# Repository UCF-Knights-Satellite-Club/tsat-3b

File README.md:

# tsat-3b

TSat-3B: a 1.5U CubeSat that is dropped from a tethered balloon and flies itself back to the launch site under a guided parafoil.
This repo holds the flight software and every circuit board.

## What's here

| Folder | What it is | Status |
|---|---|---|
| [`FlightController/`](FlightController/) | ESP32 guided-parafoil flight software (Arduino sketch) plus a PC simulator | Guidance done and tested in simulation; sensor drivers still stubbed |
| [`PowerDistributionBoard/1.5U-Rev1/`](PowerDistributionBoard/1.5U-Rev1/) | Power board candidate (Eric P.): carrier for plug-in buck modules | Under review |
| [`PowerDistributionBoard/TPSM63610/`](PowerDistributionBoard/TPSM63610/) | Power board candidate (Lawson H.): on-board TPSM63610 regulators | Under review |
| [`PowerDistributionBoard/RevB-SY8105/`](PowerDistributionBoard/RevB-SY8105/) | Earlier power board (Lawson H.), on-board SY8105 regulators | Superseded |
| [`MainBoard/`](MainBoard/) | Flight computer board (Pablo J.): ESP32, IMU, GPS, barometer, LoRa | Not uploaded yet |

Two power board designs are being reviewed to pick the one going forward. See [`PowerDistributionBoard/README.md`](PowerDistributionBoard/README.md) for how they compare.

## Contributing

Read [`CONTRIBUTING.md`](CONTRIBUTING.md) before you upload anything. In short: upload the KiCad project together with its
Gerbers, put files in the right folder, don't upload zips of whole projects, and write one sentence in the PR description.

## License

- Software (`FlightController/`): [MIT](LICENSE)
- Hardware designs (`PowerDistributionBoard/`, `MainBoard/`): [CERN Open Hardware Licence v2, Permissive (CERN-OHL-P-2.0)](LICENSE-HARDWARE)

Copyright (c) 2026 Knights Satellite Club

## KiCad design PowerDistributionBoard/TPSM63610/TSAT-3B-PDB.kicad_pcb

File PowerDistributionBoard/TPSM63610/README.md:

# TSAT-3B-PDB (on-board TPSM63610 regulators)

<p align="center">
  <b>Candidate, under review</b> &nbsp;·&nbsp; Designer: Lawson H. &nbsp;·&nbsp; 70 × 67 mm &nbsp;·&nbsp; 2-layer &nbsp;·&nbsp; KiCad 10
</p>

| Top | Bottom |
|:---:|:---:|
|  |  |

📄 **Schematic:** [PDF](docs/schematic.pdf) &nbsp;·&nbsp; 🧾 **BOM:** [CSV with suppliers](bom/TSAT-3B-PDB_BOM.csv)
&nbsp;·&nbsp; 🔌 **Wiring:** [notes](docs/wiring.md) &nbsp;·&nbsp; 📝 [Review log](docs/review-notes.md)

70 parts. Two TI TPSM63610 buck modules on the board make 5.0 V logic and 7.2 V servo power from a 3S battery. It also has a main
input switch, fused outputs for two servos, a nichrome cutter channel, external brake resistors, battery voltage sensing and a 5 V
output for a camera board. Some 3D models are missing, so the renders show bare pads for the TPSM63610s and a few connectors.

- Open `TSAT-3B-PDB.kicad_pro` in KiCad 10. The symbol and footprint libraries it needs are in `Libraries/`.
- No Gerbers yet. Export them once this design is chosen.

Unpacked from `TSAT-3B-PDB.zip` (uploaded in PR #2). The lock files, KiCad local settings, the `.history/` folder and the review
tool output (`Review/`, `.patch`) from that zip were left out.

## Review

Design review feedback is tracked in [issue #8](https://github.com/UCF-Knights-Satellite-Club/tsat-3b/issues/8).

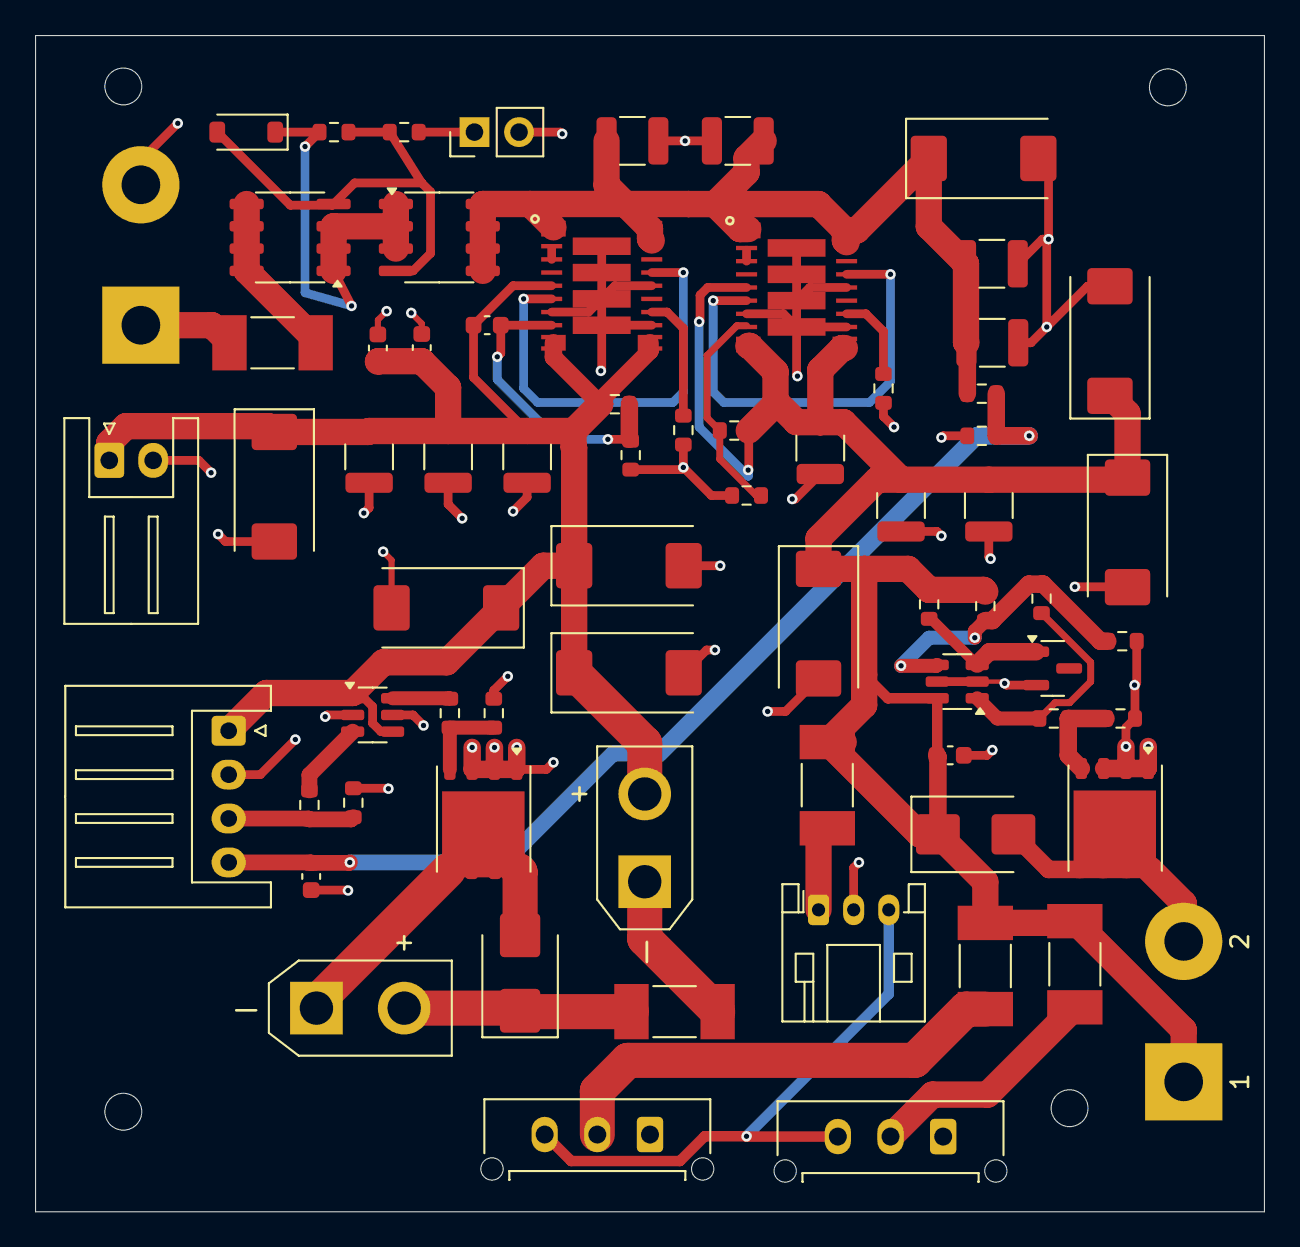
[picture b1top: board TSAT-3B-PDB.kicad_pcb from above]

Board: 2 copper layers, 70.0 x 67.0 mm, 74 parts (0 on the bottom side), 34 nets.

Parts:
C1, C3, C7, C8, C12, C13, C14, C19, C24, C32: 22u / 25V X7R; C_1210_3225Metric
C4, C16, C33: 100n / 50V; C_0603_1608Metric
C15, C35, C36: 220u / 16V POLY; CP_EIA-7343-31_Kemet-D
C17, C18: 100u / 25V POLY; CP_EIA-7343-31_Kemet-D
C22: 22p / 50V C0G; C_0603_1608Metric
C25, C26, C27: 220u / 10V POLY; CP_EIA-7343-31_Kemet-D
C31: 1u / 16V X7R; C_0603_1608Metric
D1: BZT52C10; D_SOD-123
D4, D6: B340B; D_SMB
D5: LM4040A25; SOT-23
F1: 15A SMD; Fuse_Littelfuse-NANO2-451_453
F2: 7A; Fuse_Littelfuse-NANO2-451_453
F3, F4: 5A branch; Fuse_Littelfuse-NANO2-451_453
F5: 1A adapter branch; Fuse_Littelfuse-NANO2-451_453
H1, H2, H3, H4: MountingHole_2.1mm
J1: 3S BATTERY; CablePads_2x_D2.2_P8mm
J2: MAIN PCB; JST_XH_S4B-XH-A_1x04_P2.50mm_Horizontal
J3: ADAPTER PWR+D; JST_PH_S3B-PH-K_1x03_P2.00mm_Horizontal
J4: CUTTER ARM; AMASS_XT30UPB-M_P1_Positive
J5: NICHROME; AMASS_XT30UPB-M_P1_Positive
J6: CAMERA PCB; JST_XH_S2B-XH-A_1x02_P2.50mm_Horizontal
J7, J8: SERVO MICRO-FIT; Molex_Micro-Fit_3.0_43650-0315_1x03_P3.00mm_Vertical
J9: REMOTE BRAKE RESISTORS; CablePads_2x_D2.2_P8mm
JP1: MAIN ON LINK; PinHeader_1x02_P2.54mm_Vertical
Q1, Q4: BSC009NE2LS5; Infineon_PG-TDSON-8_6.15x5.15mm
Q2, Q3: FDS6679AZ; SOIC-8_3.9x4.9mm_P1.27mm
R1: 100k; R_0603_1608Metric
R2, R12, R13, R20, R23: 10k; R_0603_1608Metric
R3, R5: 100k 1%; R_0603_1608Metric
R4: 24.9k 1%; R_0603_1608Metric
R6: 22k 1%; R_0603_1608Metric
R8: 62k 0.1%; R_0603_1608Metric
R9, R19: 10k 0.1%; R_0603_1608Metric
R10, R21: 15.8k 1%; R_0603_1608Metric
R11, R22: 22R; R_0603_1608Metric
R16: 1k; R_0603_1608Metric
R18: 21.5k 0.1%; R_0603_1608Metric
R24: 806k 1%; R_0603_1608Metric
U1, U2: TPSM63610RDFR; TPSM63610_RDF22_MfrLand
U3: MCP14A0052T-E/CH; SOT-23-6
U4: TLV1805DBVR; SOT-23-6

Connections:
+5V: C3.1, C16.1, C18.1, C22.1, C24.1, C25.1, C26.1, C27.1, C31.1, C32.1, J2.1, J4.1, J6.1, R3.1, U1.5 (VLDOIN), U1.9 (VOUT), U1.10 (VOUT), U3.1 (VDD), U3.4 (EN)
ADAPTER_7V2: F5.2, J3.1
BRAKE_DRAIN: D6.2 (A), J9.2, Q4.5 (D)
BRAKE_GATE: Q4.4 (G), R22.2, R23.1
BRAKE_OUT: R22.1, R24.1, U4.1 (OUT)
BRAKE_SENSE: R18.2, R19.1, R24.2, U4.4 (IN+)
CUT_IN: R16.2, U3.3 (IN)
CUT_PWM: J2.3, R13.1, R16.1
CUT_PWR: F2.1, J4.2
GND: C1.2, C3.2, C4.2, C7.2, C8.2, C12.2, C13.2, C14.2, C15.2, C16.2, C17.2, C18.2, C19.2, C24.2, C25.2, C26.2, C27.2, C31.2, C32.2, C33.2, C35.2, C36.2, D5.2 (A), J1.2, J2.2, J3.2, J6.2, J7.1, J8.1, JP1.2 (B), Q1.1 (S), Q1.2 (S), Q1.3 (S), Q4.1 (S), Q4.2 (S), Q4.3 (S), R4.2, R6.2, R9.2, R10.2, R12.2, R13.2, R19.2, R21.2, R23.2, U1.7 (AGND), U1.11 (AGND), U1.14 (SPSP), U1.19 (PGND), U1.20 (PGND), U1.21 (AGND), U1.22 (AGND), U2.7 (AGND), U2.11 (AGND), U2.14 (SPSP), U2.19 (PGND), U2.20 (PGND), U2.21 (AGND), U2.22 (AGND), U3.2 (AGND), U3.5 (GND), U4.2 (V-), U4.5 (SHDN)
HEATER_LOW: D4.2 (A), J5.2, Q1.5 (D)
HEATER_PLUS: D4.1 (K), F2.2, J5.1
MAIN_SOURCES: D1.1 (K), Q2.1 (S), Q2.2 (S), Q2.3 (S), Q3.1 (S), Q3.2 (S), Q3.3 (S), R1.1
unnamed: D1.2 (A), Q2.4 (G), Q3.4 (G), R1.2, R2.1
unnamed: D5.1 (K), R20.2, U4.3 (IN-)
unnamed: F1.2, Q2.5 (D), Q2.6 (D), Q2.7 (D), Q2.8 (D)
unnamed: JP1.1 (A), R2.2
unnamed: Q1.4 (G), R11.2, R12.1
unnamed: U1.2 (RBOOT), U1.3 (CBOOT)
unnamed: C22.2, R3.2, R4.1, U1.8 (FB)
unnamed: R21.1, U1.12 (RT)
unnamed: U2.2 (RBOOT), U2.3 (CBOOT)
unnamed: R8.2, R9.1, U2.8 (FB)
unnamed: R10.1, U2.12 (RT)
unnamed: R11.1, U3.6 (OUT)
SERVO1_V: F3.2, J7.2
SERVO2_V: F4.2, J8.2
SERVO_D: J3.3, J7.3, J8.3
U1_VCC: U1.6 (VCC), U1.15 (MODE)
U2_VCC: U2.6 (VCC), U2.15 (MODE)
VBAT_RAW: F1.1, J1.1
VBAT_SENSE: C4.1, J2.4, R5.2, R6.1
VBUS: C1.1, C7.1, C8.1, C17.1, C19.1, Q3.5 (D), Q3.6 (D), Q3.7 (D), Q3.8 (D), R5.1, U1.1 (VIN), U1.17 (EN), U1.18 (VIN), U2.1 (VIN), U2.17 (EN), U2.18 (VIN)
VSERVO_7V2: C12.1, C13.1, C14.1, C15.1, C33.1, C35.1, C36.1, D6.1 (K), F3.1, F4.1, F5.1, J9.1, R8.1, R18.1, R20.1, U2.5 (VLDOIN), U2.9 (VOUT), U2.10 (VOUT), U4.6 (V+)

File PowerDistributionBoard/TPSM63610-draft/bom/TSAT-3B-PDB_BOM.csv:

References,Quantity,Value,Footprint,Manufacturer,MPN,US supplier,Listed stock,Checked date,Purchase link,Assembly / mating notes
"C15, C35, C36",3,220u / 16V POLY,TSAT3B:CP_EIA-7343-31_Kemet-D,KEMET,T521D227M016ATE025,DigiKey,180,2026-11-14,https://www.digikey.com/en/products/detail/kemet/T521D227M01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,
"C16, C33, C4",3,100n / 50V,TSAT3B:C_0603_1608Metric,KEMET,C0603C104K5RACTU,DigiKey,2137059,2026-11-14,https://www.digikey.com/en/products/detail/kemet/C0603C104K5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,
"C17, C18",2,100u / 25V POLY,TSAT3B:CP_EIA-7343-31_Kemet-D,KEMET,T521D107M025ATE040,DigiKey,2244,2026-11-14,https://www.digikey.com/en/products/detail/kemet/T521D107M02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,
C22,1,22p / 50V C0G,TSAT3B:C_0603_1608Metric,KEMET,C0603C220J5GACTU,DigiKey,286780,2026-11-13,https://www.digikey.com/en/products/detail/kemet/C0603C220J5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,
"C25, C26, C27",3,220u / 10V POLY,TSAT3B:CP_EIA-7343-31_Kemet-D,KEMET,T520D227M010ATE018,DigiKey,73,2026-11-14,https://www.digikey.com/en/products/detail/kemet/T520D227M01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,
"C1, C12, C13, C14, C19, C24, C3, C32, C7, C8",10,22u / 25V X7R,TSAT3B:C_1210_3225Metric,Taiyo Yuden,TMK325B7226MM-TR,DigiKey,4608,2026-11-14,https://www.digikey.com/en/products/detail/taiyo-yuden/TMK32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,
C31,1,1u / 16V X7R,TSAT3B:C_0603_1608Metric,KEMET,C0603C105K4RACTU,DigiKey,3008570,2026-11-14,https://www.digikey.com/en/products/detail/kemet/C0603C105K4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,
D1,1,BZT52C10,TSAT3B:D_SOD-123,Vishay,BZT52C10-E3-18,DigiKey,7745,2026-11-14,https://www.digikey.com/en/products/detail/vishay-general-se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,
"D4, D6",2,B340B,TSAT3B:D_SMB,Diodes Inc.,B340B-13-F,DigiKey,847,2026-11-14,https://www.digikey.com/en/products/detail/diodes-incorporat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,
D5,1,LM4040A25,TSAT3B:SOT-23,Texas Instruments,LM4040A25IDBZR,DigiKey,5237,2026-11-13,https://www.digikey.com/en/products/detail/texas-instruments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,
F1,1,15A SMD,TSAT3B:Fuse_Littelfuse-NANO2-451_453,Littelfuse,0451015.MRL,DigiKey,11974,2026-11-14,https://www.digikey.com/en/products/detail/littelfuse-inc/04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,
F2,1,7A,TSAT3B:Fuse_Littelfuse-NANO2-451_453,Littelfuse,0451007.MRL,DigiKey,18709,2026-11-14,https://www.digikey.com/en/products/detail/littelfuse-inc/04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,
"F3, F4",2,5A branch,TSAT3B:Fuse_Littelfuse-NANO2-451_453,Littelfuse,0451005.MRL,DigiKey,21323,2026-11-14,https://www.digikey.com/en/products/detail/littelfuse-inc/04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,
F5,1,1A adapter branch,TSAT3B:Fuse_Littelfuse-NANO2-451_453,Littelfuse,0451001.MRL,DigiKey,2608,2026-11-14,https://www.digikey.com/en/products/detail/littelfuse-inc/04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,
J1,1,3S BATTERY,TSAT3B:CablePads_2x_D2.2_P8mm,,Deans mating pigtail,User-supplied / fabricated,not verified,,,"Deans/T-plug mating pigtail to actual battery. Solder: 1 battery positive, 2 GND. No PCB header added."
J2,1,MAIN PCB,TSAT3B:JST_XH_S4B-XH-A_1x04_P2.50mm_Horizontal,JST,S4B-XH-A(LF)(SN),DigiKey,3599,2026-11-14,https://www.digikey.com/en/products/detail/jst-sales-america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,"Cable mate: XHP-4 + SXH-001T-P0.6 (22–28 AWG). Pins 1 +5V, 2 GND, 3 CUT_PWM, 4 VBAT_SENSE. Check remote main-PCB pinout."
J3,1,ADAPTER PWR+D,TSAT3B:JST_PH_S3B-PH-K_1x03_P2.00mm_Horizontal,JST,S3B-PH-K-S(LF)(SN),DigiKey,"47,840",2026-11-14,https://www.digikey.com/en/products/detail/jst-sales-america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,"Cable mate: PHR-3 + SPH-002T-P0.5S (24–30 AWG). 1 adapter +7.2V, 2 GND, 3 servo D. Split to green power input and servo-port D only. Separate ESP UART TX/RX/GND cable required."
J4,1,CUTTER ARM,TSAT3B:AMASS_XT30UPB-M_P1_Positive,,XT30UPB-M30,Jameco,231,2026-11-14,https://www.jameco.com/z/XT30UPB-M30-Amass-XT30-Socket-Male-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,Cable mate: XT30U-F. Insulated shorting loop between contacts makes cutter ARM link. Neither J4 contact is a normal GND output.
J5,1,NICHROME,TSAT3B:AMASS_XT30UPB-M_P1_Positive,,XT30UPB-M30,Jameco,231,2026-11-14,https://www.jameco.com/z/XT30UPB-M30-Amass-XT30-Socket-Male-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,"Cable mate: XT30U-F. 1 HEATER_PLUS, 2 HEATER_LOW, to nichrome terminals."
J6,1,CAMERA PCB,TSAT3B:JST_XH_S2B-XH-A_1x02_P2.50mm_Horizontal,JST,S2B-XH-A(LF)(SN),DigiKey,23660,2026-11-14,https://www.digikey.com/en/products/detail/jst-sales-america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,"Cable mate: XHP-2 + SXH-001T-P0.6 (22–28 AWG). 1 +5V, 2 GND. Check remote camera-PCB pinout."
"J7, J8",2,SERVO MICRO-FIT,TSAT3B:Molex_Micro-Fit_3.0_43650-0315_1x03_P3.00mm_Vertical,Molex,0436500315,DigiKey,"14,973",2026-11-14,https://www.digikey.com/en/products/detail/molex/0436500315/283462,"Cable mate: 0436450300 + 0430300007 contacts (20–24 AWG). 1 GND, 2 fused +7.2V, 3 serial D. Factory C044 end is 5264-3P; see TSAT-3B-PDB-Wiring.md for compatible wire sizes and adapter options."
J9,1,REMOTE BRAKE RESISTORS,TSAT3B:CablePads_2x_D2.2_P8mm,HARNESS,SOLDER_LEADS,User-supplied / fabricated,not verified,,,"Solder leads to external brake resistor bank: 1 VSERVO_7V2, 2 BRAKE_DRAIN (not GND). No cable housing needed."
JP1,1,MAIN ON LINK,TSAT3B:PinHeader_1x02_P2.54mm_Vertical,Samtec,TSW-102-07-G-S,DigiKey,70923,2026-11-14,https://www.digikey.com/en/products/detail/samtec-inc/TSW-10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,"Cable mate: existing 2.54 mm two-position jumper, or SPC02SYAN. Main input ON gate-bias link, not the cutter arming plug."
"Q2, Q3",2,FDS6679AZ,TSAT3B:SOIC-8_3.9x4.9mm_P1.27mm,onsemi,FDS6679AZ,DigiKey,12982,2026-11-14,https://www.digikey.com/en/products/detail/onsemi/FDS6679AZ/1305830,
"Q1, Q4",2,BSC009NE2LS5,TSAT3B:Infineon_PG-TDSON-8_6.15x5.15mm,Infineon,BSC009NE2LS5ATMA1,DigiKey,5277,2026-11-13,https://www.digikey.com/en/products/detail/infineon-technolo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,
R1,1,100k,TSAT3B:R_0603_1608Metric,Vishay Dale,CRCW0603100KFKEA,DigiKey,2921843,2026-11-14,https://www.digikey.com/en/products/detail/vishay-dale/CRCW0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,
"R10, R21",2,15.8k 1%,TSAT3B:R_0603_1608Metric,Yageo,RC0603FR-0715K8L,DigiKey,71594,2026-11-13,https://www.digikey.com/en/products/detail/yageo/RC0603FR-07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,
"R12, R13, R2, R20, R23",5,10k,TSAT3B:R_0603_1608Metric,Yageo,RC0603FR-0710KL,Mouser,6437466,2026-11-14,https://www.mouser.com/en/ProductDetail/603-RC0603FR-0710KL,
R16,1,1k,TSAT3B:R_0603_1608Metric,Yageo,RC0603FR-071KL,DigiKey,1810288,2026-11-14,https://www.digikey.com/en/products/detail/yageo/RC0603FR-07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,
R18,1,21.5k 0.1%,TSAT3B:R_0603_1608Metric,Vishay Dale,TNPW060321K5BEEA,DigiKey,"4,875",2026-11-14,https://www.digikey.com/en/products/detail/vishay-dale/TNPW0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,
"R11, R22",2,22R,TSAT3B:R_0603_1608Metric,Vishay Dale,CRCW060322R0FKEA,DigiKey,306061,2026-11-14,https://www.digikey.com/en/products/detail/vishay-dale/CRCW0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,
R24,1,806k 1%,TSAT3B:R_0603_1608Metric,Yageo,RC0603FR-07806KL,DigiKey,"30,138",2026-11-14,https://www.digikey.com/en/products/detail/yageo/RC0603FR-07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,
"R3, R5",2,100k 1%,TSAT3B:R_0603_1608Metric,Vishay Dale,CRCW0603100KFKEA,DigiKey,2921843,2026-11-14,https://www.digikey.com/en/products/detail/vishay-dale/CRCW0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,
R4,1,24.9k 1%,TSAT3B:R_0603_1608Metric,Yageo,RC0603FR-0724K9L,DigiKey,345451,2026-11-13,https://www.digikey.com/en/products/detail/yageo/RC0603FR-07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,
R6,1,22k 1%,TSAT3B:R_0603_1608Metric,Vishay Dale,CRCW060322K0FKEA,DigiKey,"207,704",2026-11-14,https://www.digikey.com/en/products/detail/vishay-dale/CRCW0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,
R8,1,62k 0.1%,TSAT3B:R_0603_1608Metric,Yageo,RT0603BRD0762KL,DigiKey,1061,2026-11-13,https://www.digikey.com/en/products/detail/yageo/RT0603BRD07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,
"R19, R9",2,10k 0.1%,TSAT3B:R_0603_1608Metric,Vishay Dale,TNPW060310K0BEEA,DigiKey,195193,2026-11-13,https://www.digikey.com/en/products/detail/vishay-dale/TNPW0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,
"U1, U2",2,TPSM63610RDFR,TSAT3B:TPSM63610_RDF22_MfrLand,Texas Instruments,TPSM63610RDFR,DigiKey,568,2026-11-13,https://www.digikey.com/en/products/detail/texas-instruments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,
U3,1,MCP14A0052T-E/CH,TSAT3B:SOT-23-6,Microchip,MCP14A0052T-E/CH,DigiKey,2611,2026-11-14,https://www.digikey.com/en/products/detail/microchip-technol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,
U4,1,TLV1805DBVR,TSAT3B:SOT-23-6,Texas Instruments,TLV1805DBVR,DigiKey,4119,2026-11-13,https://www.digikey.com/en/products/detail/texas-instruments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,

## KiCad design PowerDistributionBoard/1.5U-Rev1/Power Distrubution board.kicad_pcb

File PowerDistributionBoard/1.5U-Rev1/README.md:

# 1.5U TSat-3B power distribution board, Rev 1.0

<p align="center">
  <b>Candidate, under review</b> &nbsp;·&nbsp; Designer: Eric P. &nbsp;·&nbsp; 70 × 70 mm &nbsp;·&nbsp; 2-layer, 1.6 mm &nbsp;·&nbsp; KiCad 10
</p>

| Top | Bottom |
|:---:|:---:|
|  |  |

📄 **Schematic:** [PDF](docs/schematic.pdf) &nbsp;·&nbsp; 🧾 **BOM:** [CSV](bom/BOM.csv) &nbsp;·&nbsp; 🏭 **Fabrication:** [Gerbers + drill](fabrication/)

This board doesn't regulate anything itself. It switches, fuses and distributes battery power, and two off-the-shelf buck modules
plug into it to make the 5 V and 7.4 V rails.

## Power tree

```
3S LiPo (J1)
  └─ D1 SS54 reverse-polarity diode
       └─ F1 7 A fuse
            └─ Q3 AO4407A P-MOSFET switch ◄── J2 remove-before-flight jumper (fitted = OFF)
                 └─ VBAT_MAIN
                      ├─ J11 → XL4015 buck module → +7V4_SERVO → J3, J4 servo headers (GND, 7.4 V, data)
                      ├─ J8  → MP1584 buck module → +5V_LOGIC  → J9 main board, J10 ESP32 camera, D3 power LED
                      └─ F2 5 A fuse → R1 (0 Ω) → J6 nichrome cutter, low side switched by Q1 AO3400A
                                                   (gate from J7; D2 lights while the cutter fires)
```

J5 carries the servo data line in from the servo adapter to both servo headers.

## Connectors

| Ref | Function | Pins |
|---|---|---|
| J1 | 3S LiPo in | 2 |
| J2 | Arm jumper. Fitted = board off; remove to power on | 2 |
| J3, J4 | Servo 1 and 2 | GND, +7.4 V, data |
| J5 | Servo data in | 2 |
| J6 | Nichrome cutter out | 2 |
| J7 | Cutter trigger in (from main board) | 2 |
| J8 | MP1584 module | VBAT, GND, +5 V, GND |
| J9 | 5 V to main board | 2 |
| J10 | 5 V to ESP32 camera | 2 |
| J11 | XL4015 module | VBAT, GND, +7.4 V, GND |

## Checks

KiCad 10 on 2026-11-17: ERC 0 errors, DRC 0 violations, 0 unconnected items, schematic and PCB match. The Gerbers in
`fabrication/` are the ones exported from this exact PCB file.

## Review

Design review feedback is tracked in [issue #7](https://github.com/UCF-Knights-Satellite-Club/tsat-3b/issues/7).

## Files

- `Power Distrubution board.kicad_pro` / `.kicad_sch` / `.kicad_pcb`: the KiCad project. The file names keep the original spelling,
  because KiCad stores the project name inside the schematic and renaming the files would break the reference designators.
- `TSAT3B.kicad_sym`: the club symbol library (AO4407A).
- `docs/`: schematic PDF and board renders, exported from the KiCad files with `kicad-cli`.
- `bom/BOM.csv`: grouped bill of materials, exported from the schematic.
- `fabrication/`: Gerbers and drill files to send to the board house.

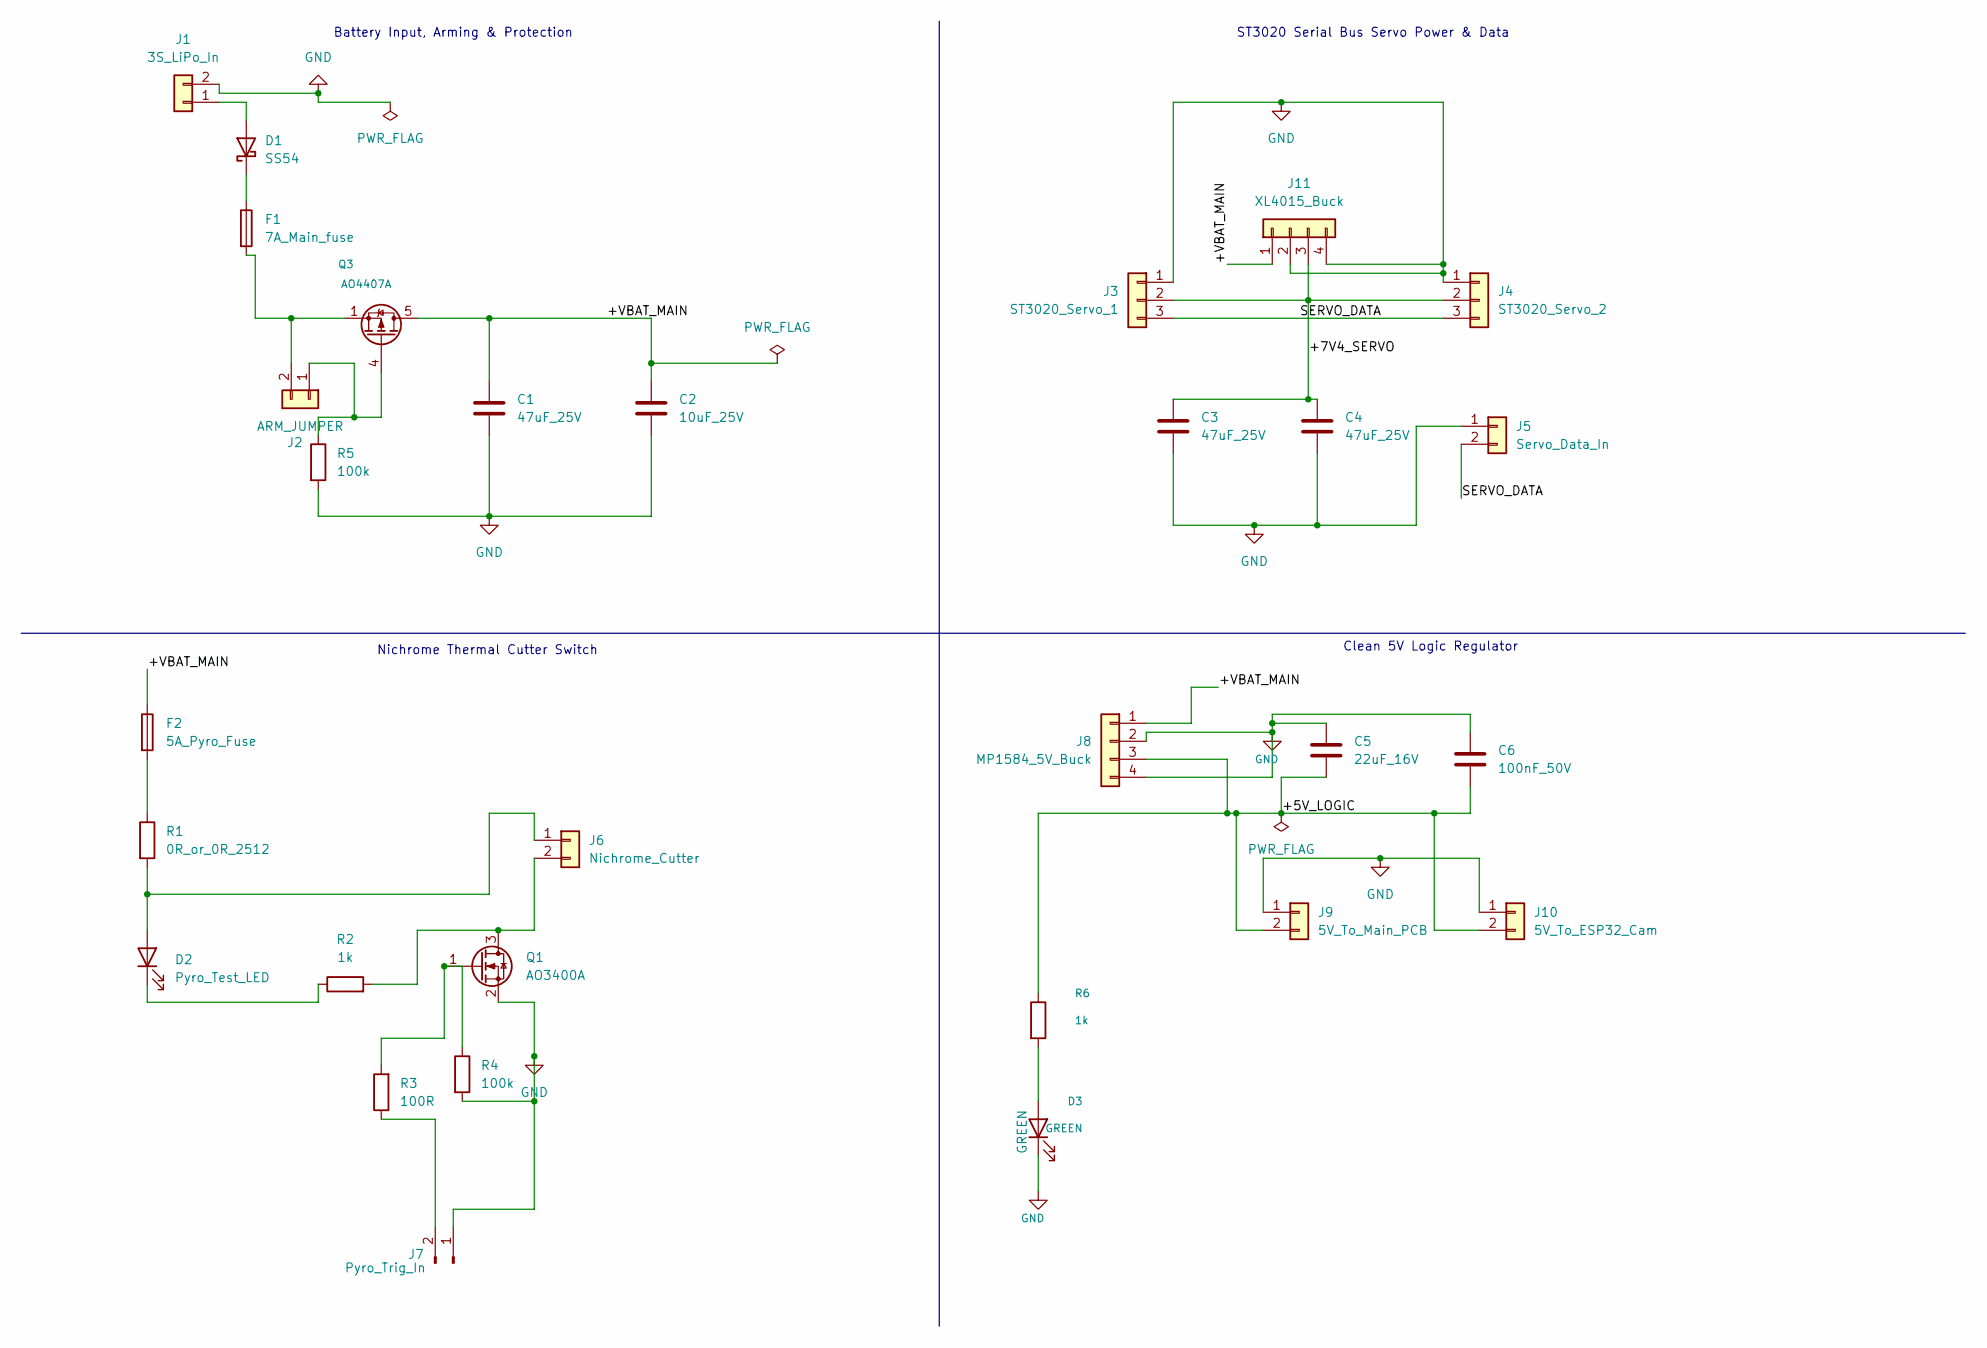
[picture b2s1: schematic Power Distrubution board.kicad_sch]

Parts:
C1, C3, C4: 47uF_25V; C_1206_3216Metric
C2: 10uF_25V; C_0805_2012Metric
C5: 22uF_16V; C_0805_2012Metric
C6: 100nF_50V; C_0805_2012Metric
D1: SS54; D_SMA
D2: Pyro_Test_LED; LED_0805_2012Metric
D3: GREEN; LED_0805_2012Metric; MPN YLED0603G
F1: 7A_Main_fuse; Fuse_1206_3216Metric
F2: 5A_Pyro_Fuse; Fuse_1206_3216Metric
J1: 3S_LiPo_In; PinHeader_1x02_P2.54mm_Horizontal
J2: ARM_JUMPER; PinHeader_1x02_P2.54mm_Horizontal
J3: ST3020_Servo_1; PinHeader_1x03_P2.54mm_Horizontal
J4: ST3020_Servo_2; PinHeader_1x03_P2.54mm_Horizontal
J5: Servo_Data_In; PinHeader_1x02_P2.54mm_Horizontal
J6: Nichrome_Cutter; PinHeader_1x02_P2.54mm_Horizontal
J7: Pyro_Trig_In; PinHeader_1x02_P2.54mm_Horizontal
J8: MP1584_5V_Buck; PinHeader_1x04_P2.54mm_Vertical
J9: 5V_To_Main_PCB; PinHeader_1x02_P2.54mm_Horizontal
J10: 5V_To_ESP32_Cam; PinHeader_1x02_P2.54mm_Horizontal
J11: XL4015_Buck; PinHeader_1x04_P2.54mm_Vertical
Q1: AO3400A; SOT-23
Q3: AO4407A; SOIC-8_3.9x4.9mm_P1.27mm; MPN AO4407A
R1: 0R_or_0R_2512; R_2512_6332Metric
R2: 1k; R_0805_2012Metric
R3: 100R; R_0805_2012Metric
R4, R5: 100k; R_0805_2012Metric
R6: 1k; R_0805_2012Metric; MPN 1RC0603F1001

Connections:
/+5V_LOGIC: C5.1, C6.1, J8.3, J9.2, J10.2, R6.1
/+7V4_SERVO: C3.1, C4.1, J3.2, J4.2, J11.3
/+VBAT_MAIN: C1.2, C2.2, F2.1, J8.1, J11.1, Q3.5 (D), Q3.6 (D), Q3.7 (D), Q3.8 (D)
/SERVO_DATA: J3.3, J4.3, J5.2
GND: C1.1, C2.1, C3.2, C4.2, C5.2, C6.2, D3.1 (K), J1.2, J3.1, J4.1, J5.1, J7.1, J8.2, J8.4, J9.1, J10.1, J11.2, J11.4, Q1.2 (S), R4.2, R5.2
unnamed: D1.2 (A), J1.1
unnamed: D1.1 (K), F1.1
unnamed: D2.2 (A), J6.1, R1.2
unnamed: D2.1 (K), R2.1
unnamed: D3.2 (A), R6.2
unnamed: F2.2, R1.1
unnamed: J2.1, Q3.4 (G), R5.1
unnamed: F1.2, J2.2, Q3.1 (S), Q3.2 (S), Q3.3 (S)
unnamed: J6.2, Q1.3 (D), R2.2
unnamed: J7.2, R3.1
unnamed: Q1.1 (G), R3.2, R4.1

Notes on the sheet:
Clean 5V Logic Regulator
Battery Input, Arming & Protection
Nichrome Thermal Cutter Switch
ST3020 Serial Bus Servo Power & Data

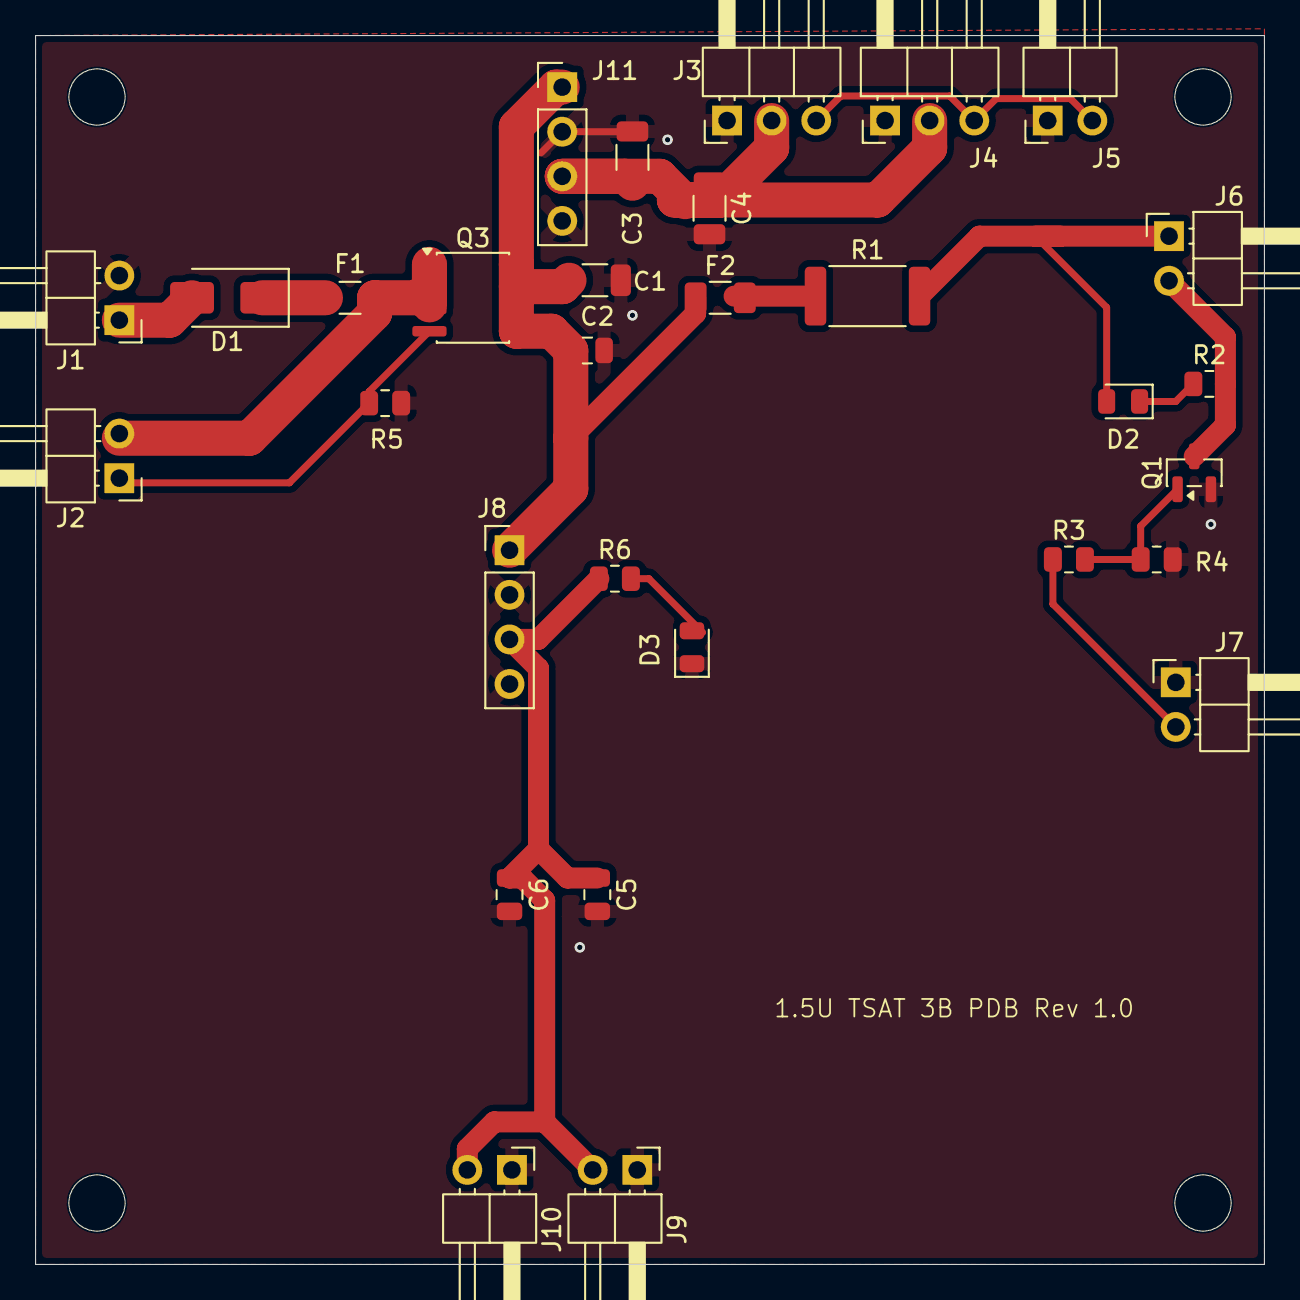
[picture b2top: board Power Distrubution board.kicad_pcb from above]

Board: 2 copper layers, 70.0 x 70.0 mm, 34 parts (0 on the bottom side), 16 nets.

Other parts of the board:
Hole1, Hole2, Hole3, Hole4: MountingHole_3.2mm_M3

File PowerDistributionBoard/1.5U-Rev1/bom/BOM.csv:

"References","Value","Footprint","Qty"
"C1,C3,C4","47uF_25V","Capacitor_SMD:C_1206_3216Metric","3"
"C2","10uF_25V","Capacitor_SMD:C_0805_2012Metric","1"
"C5","22uF_16V","Capacitor_SMD:C_0805_2012Metric","1"
"C6","100nF_50V","Capacitor_SMD:C_0805_2012Metric","1"
"D1","SS54","Diode_SMD:D_SMA","1"
"D2","Pyro_Test_LED","LED_SMD:LED_0805_2012Metric","1"
"D3","GREEN","LED_SMD:LED_0805_2012Metric","1"
"F1","7A_Main_fuse","Fuse:Fuse_1206_3216Metric","1"
"F2","5A_Pyro_Fuse","Fuse:Fuse_1206_3216Metric","1"
"J1","3S_LiPo_In","Connector_PinHeader_2.54mm:PinHeader_1x02_P2.54mm_Horizontal","1"
"J2","ARM_JUMPER","Connector_PinHeader_2.54mm:PinHeader_1x02_P2.54mm_Horizontal","1"
"J3","ST3020_Servo_1","Connector_PinHeader_2.54mm:PinHeader_1x03_P2.54mm_Horizontal","1"
"J4","ST3020_Servo_2","Connector_PinHeader_2.54mm:PinHeader_1x03_P2.54mm_Horizontal","1"
"J5","Servo_Data_In","Connector_PinHeader_2.54mm:PinHeader_1x02_P2.54mm_Horizontal","1"
"J6","Nichrome_Cutter","Connector_PinHeader_2.54mm:PinHeader_1x02_P2.54mm_Horizontal","1"
"J7","Pyro_Trig_In","Connector_PinHeader_2.54mm:PinHeader_1x02_P2.54mm_Horizontal","1"
"J8","MP1584_5V_Buck","Connector_PinHeader_2.54mm:PinHeader_1x04_P2.54mm_Vertical","1"
"J9","5V_To_Main_PCB","Connector_PinHeader_2.54mm:PinHeader_1x02_P2.54mm_Horizontal","1"
"J10","5V_To_ESP32_Cam","Connector_PinHeader_2.54mm:PinHeader_1x02_P2.54mm_Horizontal","1"
"J11","XL4015_Buck","Connector_PinHeader_2.54mm:PinHeader_1x04_P2.54mm_Vertical","1"
"Q1","AO3400A","Package_TO_SOT_SMD:SOT-23","1"
"Q3","AO4407A","Package_SO:SOIC-8_3.9x4.9mm_P1.27mm","1"
"R1","0R_or_0R_2512","Resistor_SMD:R_2512_6332Metric","1"
"R2,R6","1k","Resistor_SMD:R_0805_2012Metric","2"
"R3","100R","Resistor_SMD:R_0805_2012Metric","1"
"R4,R5","100k","Resistor_SMD:R_0805_2012Metric","2"

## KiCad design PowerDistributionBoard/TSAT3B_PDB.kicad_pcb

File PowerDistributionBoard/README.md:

# Power distribution board

The power board takes the 3S LiPo and supplies every other part of TSat-3B: the flight computer, the camera, both steering servos
and the nichrome cutter.

**Two candidate designs are being reviewed** to choose the one going forward. Rev B, Lawson H.'s earlier board, is kept for reference.

| Design | Designer | Size | Regulators | Status |
|---|---|---|---|---|
| [`1.5U-Rev1/`](1.5U-Rev1/) | Eric P. | 70 × 70 mm, 2-layer | Off-board modules: XL4015 (7.4 V servos), MP1584 (5 V logic) | **Candidate**, under review |
| [`TPSM63610/`](TPSM63610/) | Lawson H. | 70 × 67 mm, 2-layer | On-board TI TPSM63610 × 2 (5.0 V logic, 7.2 V servos) | **Candidate**, under review |
| [`RevB-SY8105/`](RevB-SY8105/) | Lawson H. | 55 × 40 mm, 2-layer | On-board Silergy SY8105 × 2 (5 V logic, ~6 V servo) | Superseded |

| 1.5U-Rev1 | TPSM63610 |
|:---:|:---:|
|  |  |

All three are KiCad 10 projects. Open the `.kicad_pro` file in each folder. Review feedback is tracked in issues: [#7 1.5U-Rev1](https://github.com/UCF-Knights-Satellite-Club/tsat-3b/issues/7), [#8 TPSM63610](https://github.com/UCF-Knights-Satellite-Club/tsat-3b/issues/8), [#10 Rev B](https://github.com/UCF-Knights-Satellite-Club/tsat-3b/issues/10).

Once a design is chosen, mark the other one superseded in this table and in its README. Don't delete it.

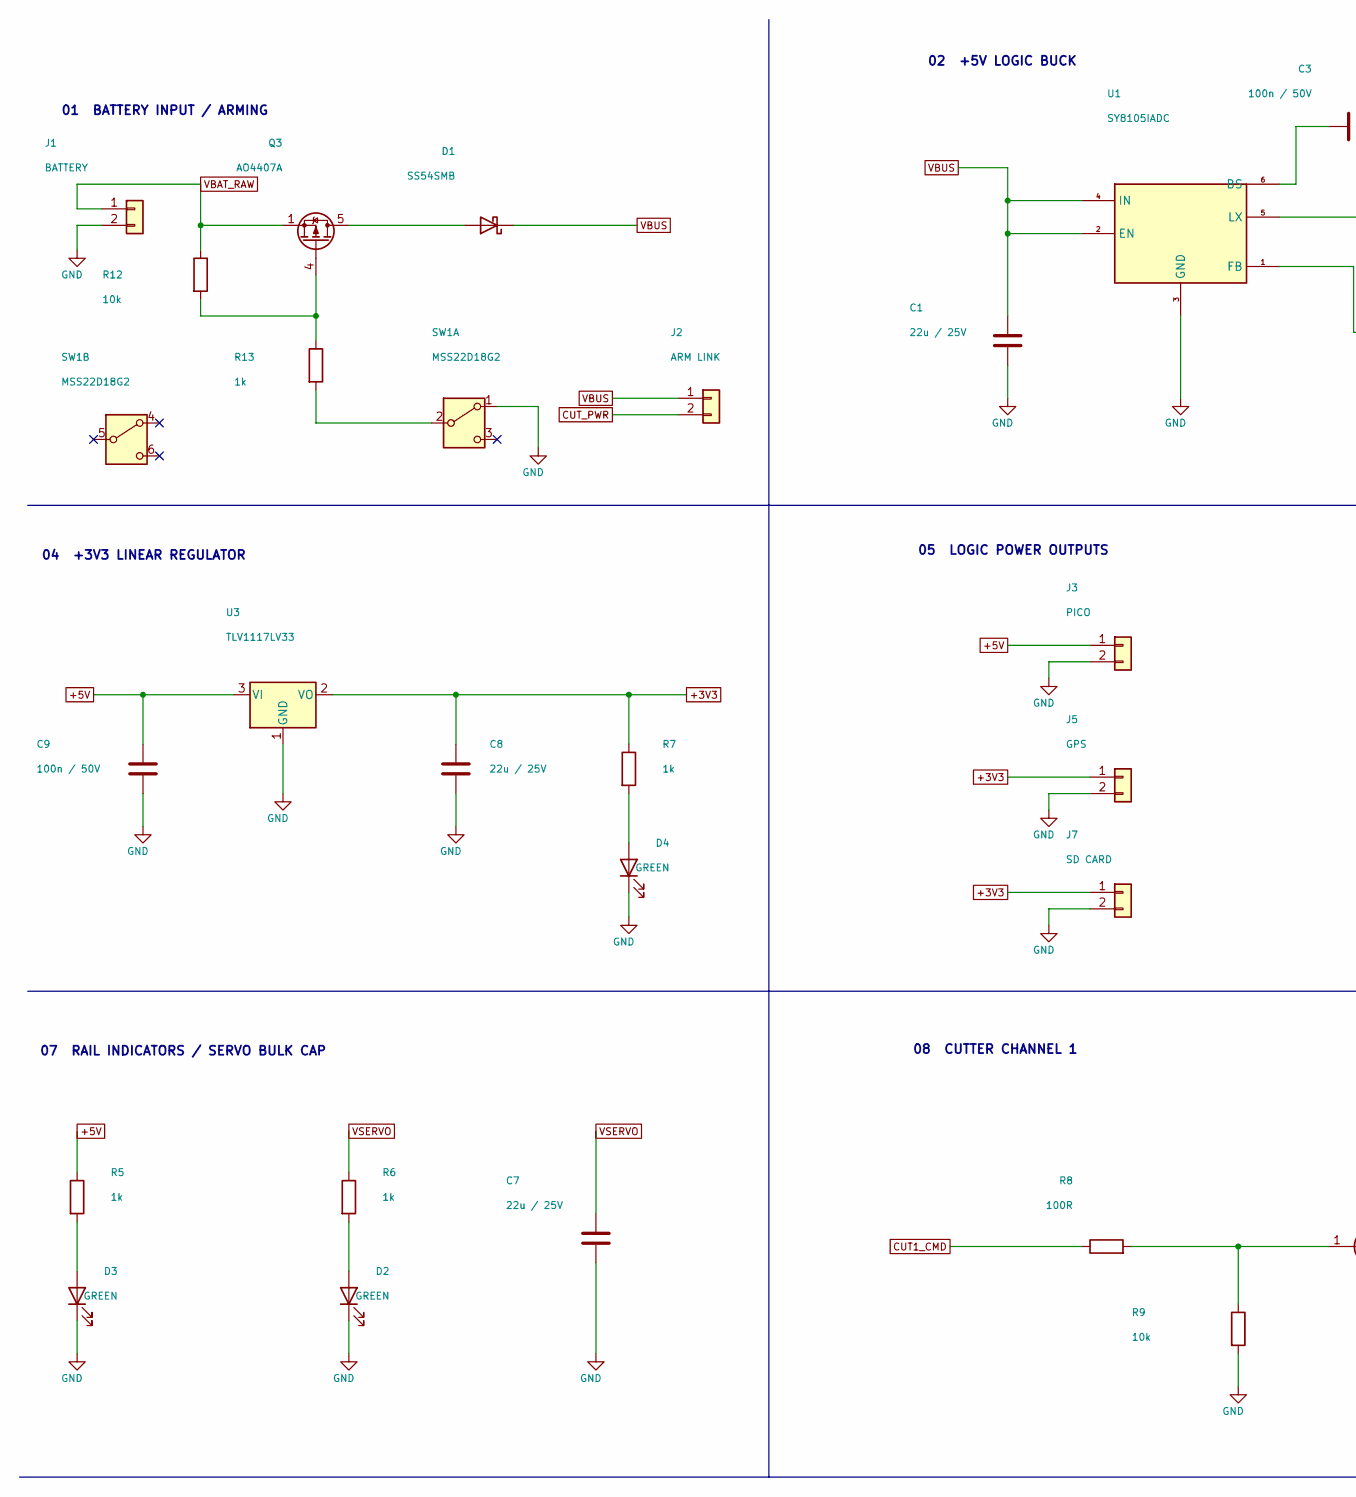
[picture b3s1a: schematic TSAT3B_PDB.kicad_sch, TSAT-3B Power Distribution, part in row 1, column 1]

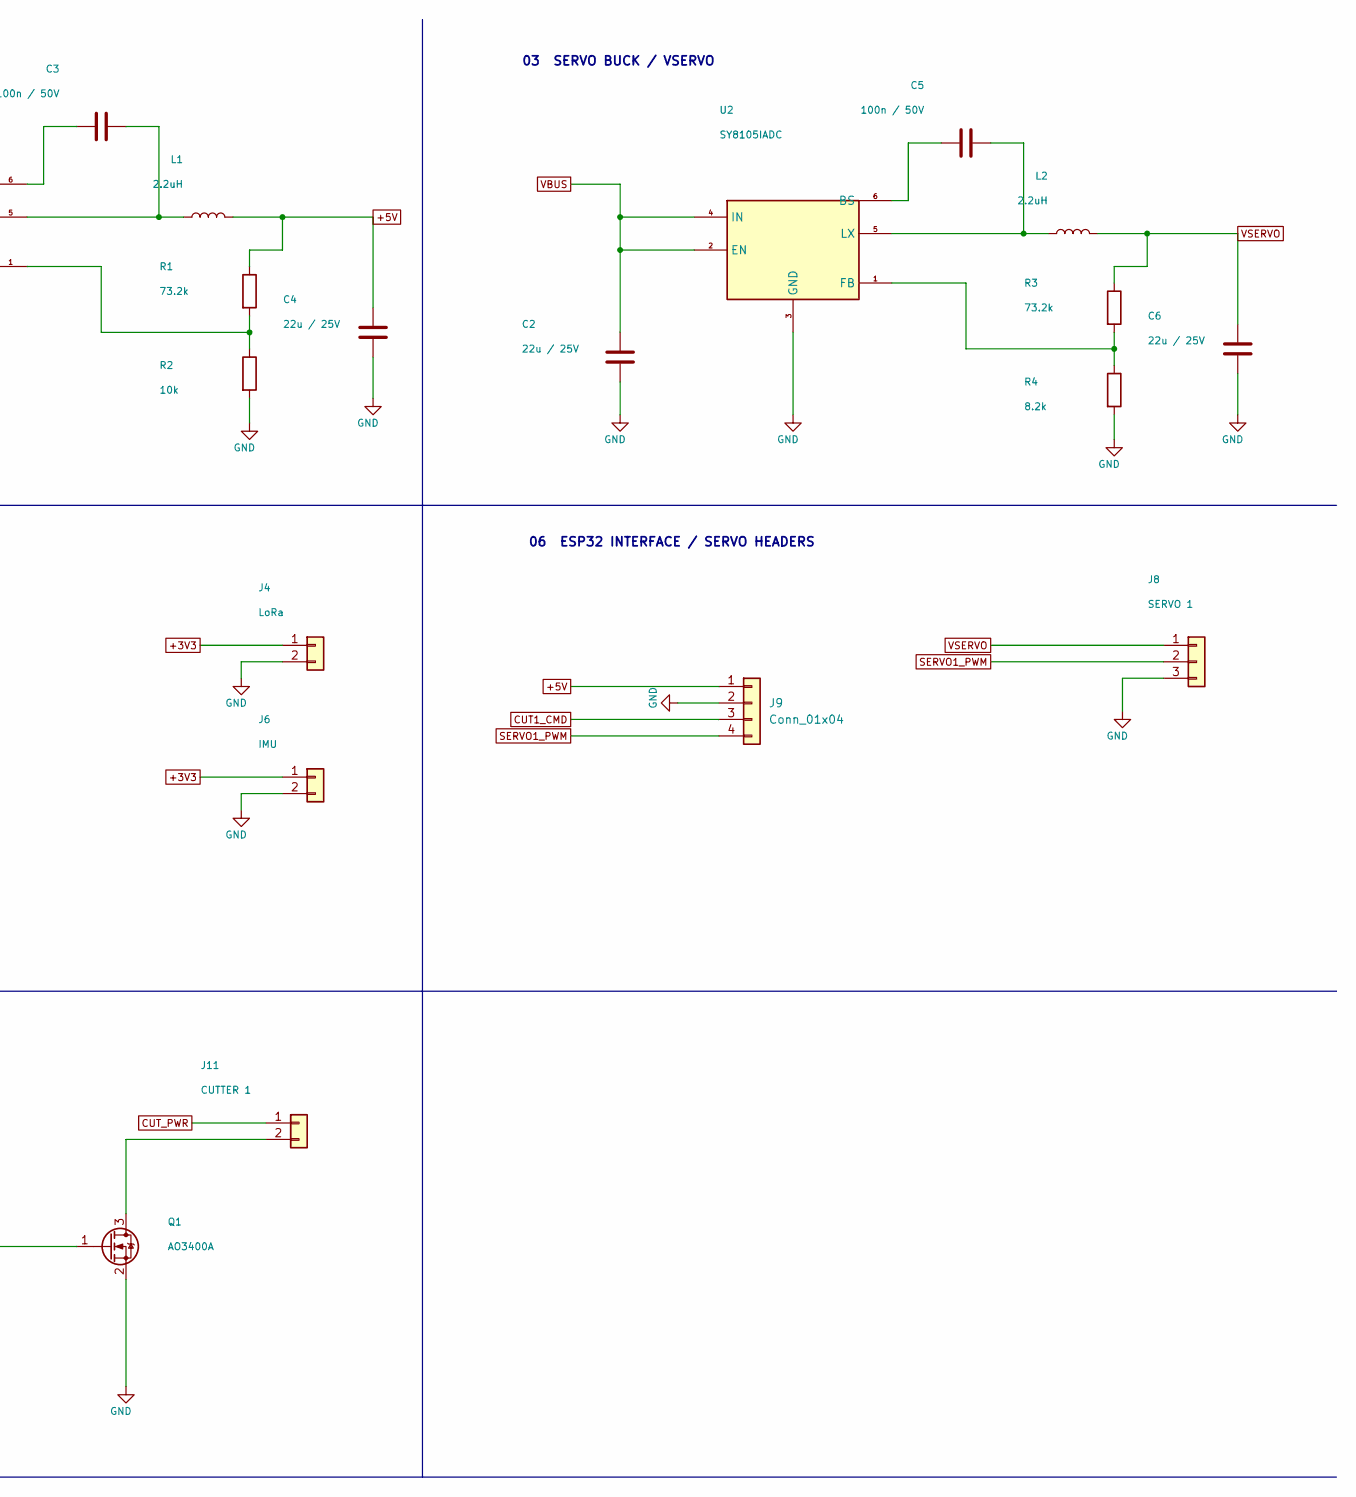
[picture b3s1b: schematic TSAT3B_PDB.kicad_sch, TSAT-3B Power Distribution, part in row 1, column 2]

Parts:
C1, C2, C4, C6, C7, C8: 22u / 25V; C_0805_2012Metric; MPN TCC0805X5R226M250FT
C3, C5, C9: 100n / 50V; C_0603_1608Metric; MPN 0603B104K500NT
D1: SS54SMB; D_SMB; MPN SS54SMB
D2, D3, D4: GREEN; LED_0603_1608Metric; MPN YLED0603G
J1: BATTERY; AMASS_XT30UPB-M_P1_Positive; MPN XT30UPB-M
J2: ARM LINK; PinHeader_1x02_P2.54mm_Vertical; MPN PZ254V-11-02P
J3: PICO; PinHeader_1x02_P2.54mm_Vertical; MPN PZ254V-11-02P
J4: LoRa; PinHeader_1x02_P2.54mm_Vertical; MPN PZ254V-11-02P
J5: GPS; PinHeader_1x02_P2.54mm_Vertical; MPN PZ254V-11-02P
J6: IMU; PinHeader_1x02_P2.54mm_Vertical; MPN PZ254V-11-02P
J7: SD CARD; PinHeader_1x02_P2.54mm_Vertical; MPN PZ254V-11-02P
J8: SERVO 1; JST_PH_B3B-PH-K_1x03_P2.00mm_Vertical; MPN 2.54-1*3P
J9: Conn_01x04; PinHeader_1x04_P2.54mm_Vertical
J11: CUTTER 1; AMASS_XT30UPB-M_P1_Positive; MPN XT30UPB-M
L1, L2: 2.2uH; L_TDK_SPM5030VT; MPN SPM5030VT-2R2M-D
Q1: AO3400A; SOT-23; MPN AO3400A
Q3: AO4407A; SOIC-8_3.9x4.9mm_P1.27mm; MPN AO4407A
R1, R3: 73.2k; R_0603_1608Metric; MPN 0603WAF7322T5E
R2, R9, R12: 10k; R_0603_1608Metric; MPN CRGCQ0603F10K
R4: 8.2k; R_0603_1608Metric; MPN FRQ0603F8201TS
R5, R6, R7, R13: 1k; R_0603_1608Metric; MPN 1RC0603F1001
R8: 100R; R_0603_1608Metric; MPN CR0603JA0101G
SW1: MSS22D18G2; SW_SHOUHAN_MSS22D18G2
U1, U2: SY8105IADC; SY8105IADC_TSOT23_6_MfrLand; MPN SY8105IADC
U3: TLV1117LV33; SOT-223-3_TabPin2; MPN TLV1117LV33DCYR

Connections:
+3V3: C8.1, J4.1, J5.1, J6.1, J7.1, R7.1, U3.2 (VO)
+5V: C4.1, C9.1, J3.1, J9.1, L1.2, R1.1, R5.1, U3.3 (VI)
CUT1_CMD: J9.3, R8.1
CUT_PWR: J2.2, J11.1
GND: C1.2, C2.2, C4.2, C6.2, C7.2, C8.2, C9.2, D2.1 (K), D3.1 (K), D4.1 (K), J1.2, J3.2, J4.2, J5.2, J6.2, J7.2, J8.3, J9.2, Q1.2 (S), R2.2, R4.2, R9.2, SW1.1 (A), U1.3 (GND), U2.3 (GND), U3.1 (GND)
unnamed: D1.2 (A), Q3.5 (D), Q3.6 (D), Q3.7 (D), Q3.8 (D)
unnamed: D2.2 (A), R6.2
unnamed: D3.2 (A), R5.2
unnamed: D4.2 (A), R7.2
unnamed: J11.2, Q1.3 (D)
unnamed: Q1.1 (G), R8.2, R9.1
unnamed: Q3.4 (G), R12.2, R13.1
unnamed: R13.2, SW1.2 (B)
unnamed: C3.1, U1.6 (BS)
unnamed: R1.2, R2.1, U1.1 (FB)
unnamed: C3.2, L1.1, U1.5 (LX)
unnamed: C5.1, U2.6 (BS)
unnamed: R3.2, R4.1, U2.1 (FB)
unnamed: C5.2, L2.1, U2.5 (LX)
SERVO1_PWM: J8.2, J9.4
VBAT_RAW: J1.1, Q3.1 (S), Q3.2 (S), Q3.3 (S), R12.1
VBUS: C1.1, C2.1, D1.1 (K), J2.1, U1.2 (EN), U1.4 (IN), U2.2 (EN), U2.4 (IN)
VSERVO: C6.1, C7.1, J8.1, L2.2, R3.1, R6.1

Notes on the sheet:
06 ESP32 INTERFACE / SERVO HEADERS
03 SERVO BUCK / VSERVO
04 +3V3 LINEAR REGULATOR
02 +5V LOGIC BUCK
01 BATTERY INPUT / ARMING
08 CUTTER CHANNEL 1
07 RAIL INDICATORS / SERVO BULK CAP
05 LOGIC POWER OUTPUTS
